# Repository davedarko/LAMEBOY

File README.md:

# LAMEBOY
https://hackaday.io/project/26823-lameboy-another-esp12-handheld

Ever since https://hackaday.io/project/18648-nokia-3310-5110-display-board I've wanted to slap on an ESP module and some buttons to make a nice little portable handheld. Now with some googling and checking out other projects how they get their stuff done and a bit time on hand while on vacation I'm using every spare minute to work on this PCB. There are some minor things I'm not sure about that need testing, but the general concept is clear.

The last version - R 3.2.3 - seems to got lost, it was rebranded to Game Toy and some pinouts were changed to make more sense.

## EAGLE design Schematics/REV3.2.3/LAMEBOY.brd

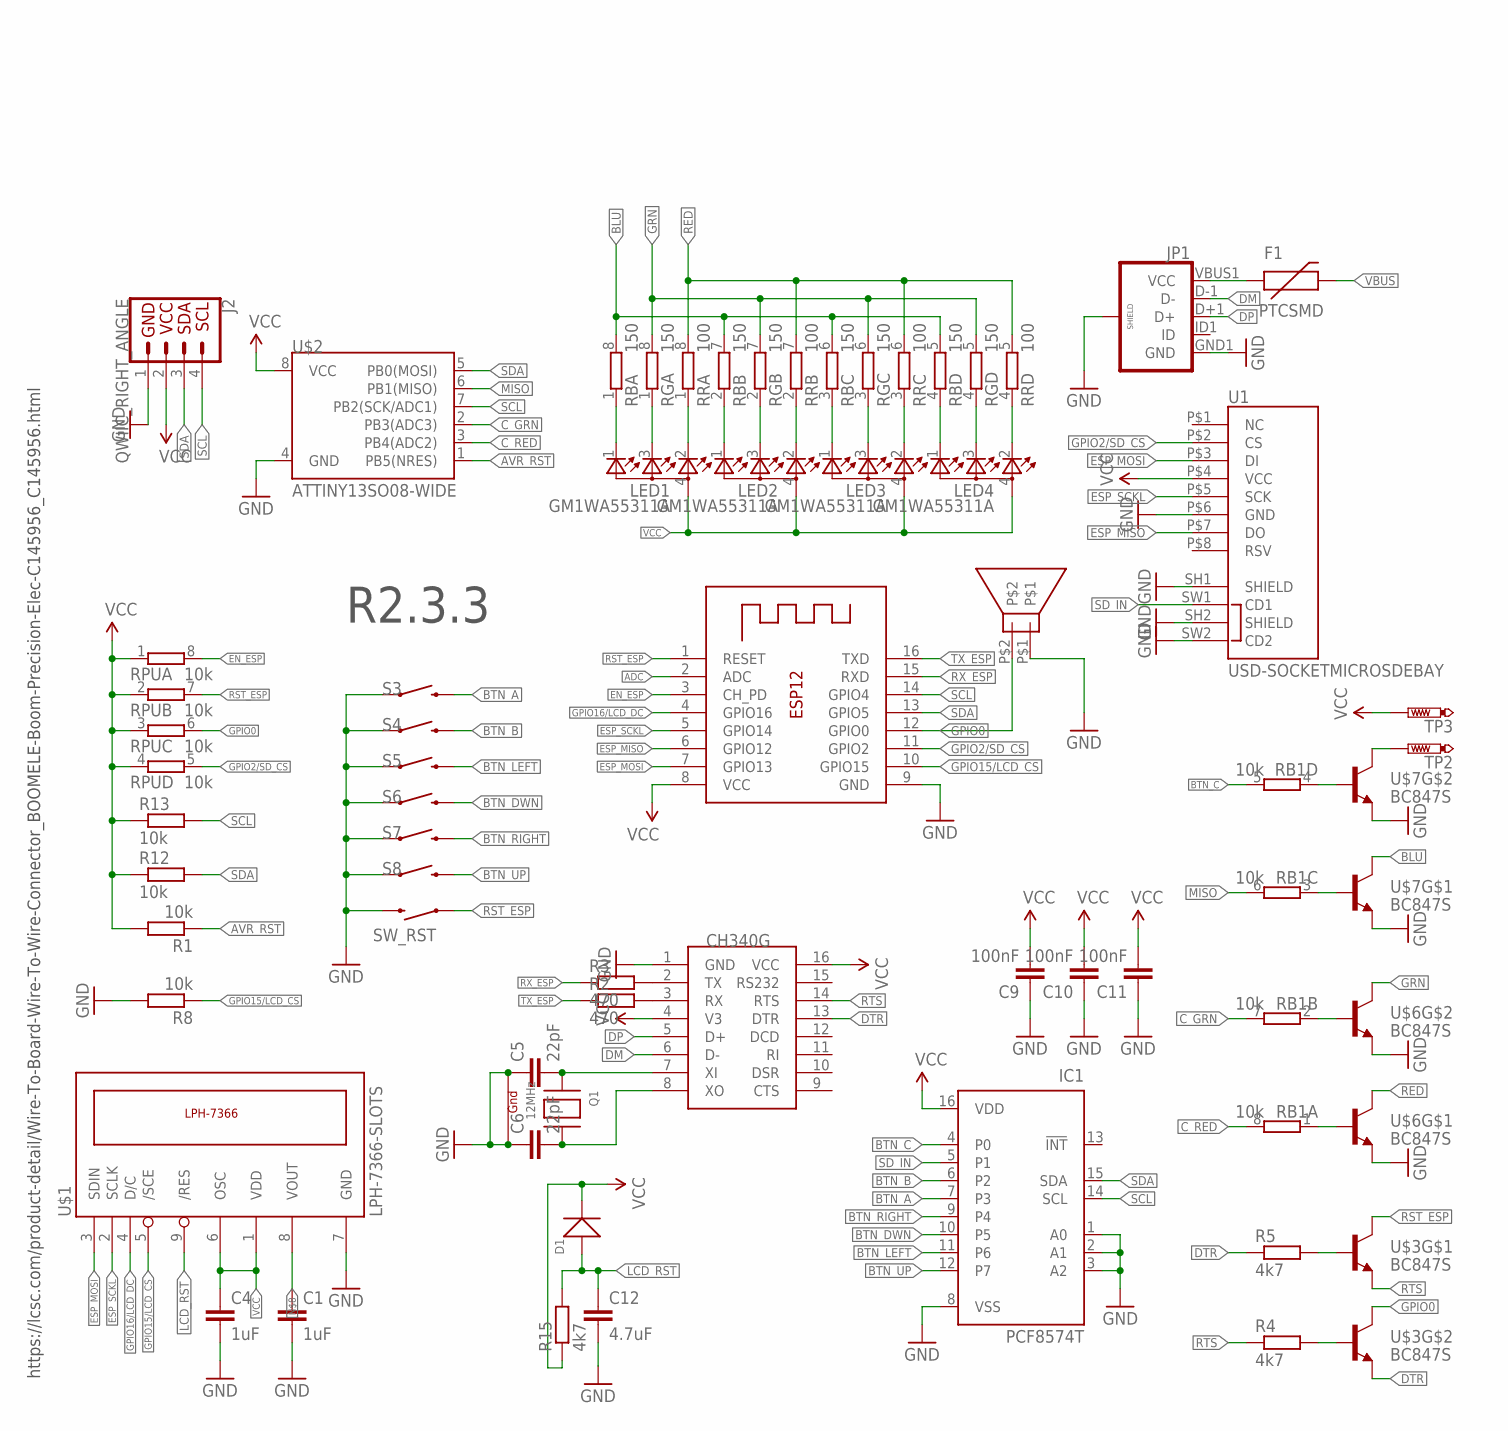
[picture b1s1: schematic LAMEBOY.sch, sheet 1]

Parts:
C1, C4: 1uF; C0805
C5, C6: 22pF; C0805
C9, C10, C11: 100nF; C0805
C12: 4.7uF; C0805
CH340G: CH340GCH340G; SOIC16
D1: DIODE'1N4148-SMD'; LL-34
F1: PTCSMD; PTC-1206
IC1: PCF8574T; SO16W
J2: QWIIC_RIGHT_ANGLE; JST04_1MM_RA
JP1: USB_MICROB_PLUG-IDK; USB-AB-MICRO-SMD_SLOT
LED1, LED2, LED3, LED4: GM1WA55311A
Q1: 12MHz; NX3225_BIGGER
R1, R8, R12, R13: 10k; R0603
R2, R3: 470; R0603
R4, R5, R15: 4k7; R0603
RB: 150; 0603-ARC
RB1: 10k; 0603-ARC
RG: 150; 0603-ARC
RPU: 10k; 0603-ARC
RR: 100; 0603-ARC
S3, S4, S5, S6, S7, S8: SWITCH-MOMENTARY-2SMD-4; TACTILE_SWITCH_TALL
SW_RST: SWITCH-MOMENTARY-2-SMD-1101NE; TACTILE-SWITCH-1101NE
TP2, TP3: PTR1B1,27; B1,27
U1: USD-SOCKETMICROSDEBAY; MICRO-SD-SOCKET-EBAY
U$1: LPH-7366-SLOTS
U$2: ATTINY13SO08-WIDE; SO08-EIAJ
U$3, U$6, U$7: BC847S; SOT363
U$5: SPEAKERKMTG-1102; KMTG-1102
X1: ESP-12

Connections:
ADC: X1.2 (ADC); also elsewhere on the board
AVR_RST: R1.1, U$2.1 (PB5(NRES))
BLU: RB.5 (2), RB.6 (2), RB.7 (2), RB.8 (2), U$7.3 (C)
BLUE_LED: LED4.1 (CGREEN), RB.4 (1)
BTN_A: IC1.7 (P3), S3.B2 (2)
BTN_B: IC1.6 (P2), S4.B2 (2)
BTN_C: IC1.4 (P0), RB1.5 (2)
BTN_DWN: IC1.10 (P5), S6.B2 (2)
BTN_LEFT: IC1.11 (P6), S5.B2 (2)
BTN_RIGHT: IC1.9 (P4), S7.B2 (2)
BTN_UP: IC1.12 (P7), S8.B2 (2)
C_GRN: RB1.7 (2), U$2.2 (PB3(ADC3))
C_RED: RB1.8 (2), U$2.3 (PB4(ADC2))
DM: CH340G.6 (D-), JP1.D-1 (D-)
DP: CH340G.5 (D+), JP1.D+1 (D+)
DTR: CH340G.13 (DTR), R5.1, U$3.1 (E)
EN_ESP: RPU.8 (2), X1.3 (CH_PD)
ESP_MISO: U1.P$7 (DO), X1.6 (GPIO12)
ESP_MOSI: U1.P$3 (DI), U$1.3 (SDIN), X1.7 (GPIO13)
ESP_SCKL: U1.P$5 (SCK), U$1.2 (SCLK), X1.5 (GPIO14)
GND: C1.2, C4.2, C5.1, C6.1, C9.1, C10.1, C11.1, C12.2, CH340G.1 (GND), IC1.1 (A0), IC1.2 (A1), IC1.3 (A2), IC1.8 (VSS), J2.1, JP1.GND1 (GND), JP1.P$1 (SHIELD), JP1.P$2 (SHIELD), JP1.P$3 (SHIELD), JP1.P$4 (SHIELD), Q1.2 (G2), Q1.4 (G1), R8.2, S3.A2 (1), S4.A2 (1), S5.A2 (1), S6.A2 (1), S7.A2 (1), S8.A2 (1), SW_RST.P$2 (2), U1.P$6 (GND), U1.SH1 (SHIELD), U1.SH2 (SHIELD), U1.SW2 (CD2), U$1.7 (GND), U$2.4 (GND), U$5.P$1, U$6.1 (E), U$6.4 (E), U$7.1 (E), U$7.4 (E), X1.9 (GND); also elsewhere on the board
GPIO0: RPU.6 (2), U$3.6 (C), U$5.P$2, X1.12 (GPIO0)
GPIO2/SD_CS: RPU.5 (2), U1.P$2 (CS), X1.11 (GPIO2)
GPIO15/LCD_CS: R8.1, U$1.5 (/SCE), X1.10 (GPIO15)
GPIO16/LCD_DC: U$1.4 (D/C), X1.4 (GPIO16)
GREEN_LED: LED4.3 (CBLUE), RG.4 (1)
GRN: RG.5 (2), RG.6 (2), RG.7 (2), RG.8 (2), U$6.6 (C)
L2_R: LED1.3 (CBLUE), RG.1
L3_B: LED1.1 (CGREEN), RB.1
L4_G: LED1.2 (CRED), RR.1
LCD_RST: C12.1, D1.A (+), R15.2, U$1.9 (/RES)
MISO: RB1.6 (2), U$2.6 (PB1(MISO))
unnamed: LED3.1 (CGREEN), RB.3 (1)
unnamed: LED3.3 (CBLUE), RG.3 (1)
unnamed: LED3.2 (CRED), RR.3 (1)
unnamed: LED2.1 (CGREEN), RB.2 (1)
unnamed: C1.1, U$1.8 (VOUT)
unnamed: LED2.3 (CBLUE), RG.2 (1)
unnamed: LED2.2 (CRED), RR.2 (1)
unnamed: RB1.1, U$6.5 (B)
unnamed: RB1.2 (1), U$6.2 (B)
unnamed: TP2.TP, U$7.6 (C)
unnamed: C5.2, CH340G.7 (XI), Q1.1 (X1)
unnamed: RB1.3 (1), U$7.5 (B)
unnamed: RB1.4 (1), U$7.2 (B)
unnamed: C6.2, CH340G.8 (XO), Q1.3 (X2)
unnamed: R5.2, U$3.5 (B)
unnamed: CH340G.3 (RX), R2.2
unnamed: CH340G.2 (TX), R3.2
unnamed: R4.2, U$3.2 (B)
RED: RR.5 (2), RR.6 (2), RR.7 (2), RR.8 (2), U$6.3 (C)
RED_LED: LED4.2 (CRED), RR.4 (1)
RST_ESP: RPU.7 (2), SW_RST.P$1 (1), U$3.3 (C), X1.1 (RESET)
RTS: CH340G.14 (RTS), R4.1, U$3.4 (E)
RX_ESP: R3.1, X1.15 (RXD)
SCL: IC1.14 (SCL), J2.4, R13.2, U$2.7 (PB2(SCK/ADC1)), X1.14 (GPIO4)
SDA: IC1.15 (SDA), J2.3, R12.2, U$2.5 (PB0(MOSI)), X1.13 (GPIO5)
SD_IN: IC1.5 (P1), U1.SW1 (CD1)
TX_ESP: R2.1, X1.16 (TXD)
VBUS: F1.2; also elsewhere on the board
VCC: C4.1, C9.2, C10.2, C11.2, CH340G.4 (V3), CH340G.16 (VCC), D1.C (-), IC1.16 (VDD), J2.2, LED1.4 (A), LED2.4 (A), LED3.4 (A), LED4.4 (A), R1.2, R12.1, R13.1, R15.1, RPU.1, RPU.2 (1), RPU.3 (1), RPU.4 (1), TP3.TP, U1.P$4 (VCC), U$1.1 (VDD), U$1.6 (OSC), U$2.8 (VCC), X1.8 (VCC); also elsewhere on the board
VUSB: F1.1, JP1.VBUS1 (VCC)

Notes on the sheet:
R2.3.3
https://lcsc.com/product-detail/Wire-To-Board-Wire-To-Wire-Connector_BOOMELE-Boom-Precision-Elec-C145956_C145956.html

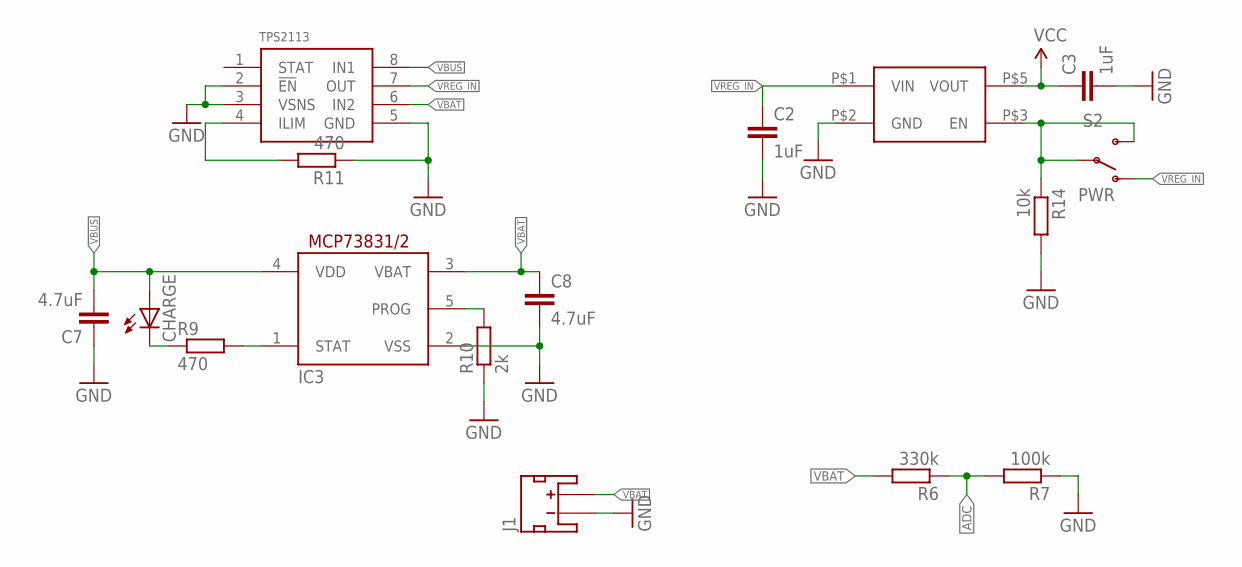
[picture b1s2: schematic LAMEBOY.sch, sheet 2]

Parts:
C2, C3: 1uF; C0805
C7, C8: 4.7uF; C0805
CHARGE: LEDCHARLIE; CHIPLED_0603_CHARLIE
IC3: MCP73831; SOT23-5L
J1: JST_2MM_MALE; JST-2-SMD
R6: 330k; R0603
R7: 100k; R0603
R9, R11: 470; R0603
R10: 2k; R0603
R14: 10k; R0603
S2: PWR; SWITCH-SPST-SMD-A
U$4: TPS2113-PW; TEXAS-PW
U$9: AP2112KAP2112K; AP2112

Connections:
ADC: R6.1, R7.2; also elsewhere on the board
GND: C2.2, C3.2, C7.1, C8.2, IC3.2 (VSS), J1.1 (-), R7.1, R10.1, R11.1, R14.2, U$4.2 (!EN), U$4.3 (VSNS), U$4.5 (GND), U$9.P$2 (GND); also elsewhere on the board
unnamed: IC3.1 (STAT), R9.2
unnamed: CHARGE.C, R9.1
unnamed: R11.2, U$4.4 (ILIM)
unnamed: IC3.5 (PROG), R10.2
VBAT: C8.1, IC3.3 (VBAT), J1.2 (+), R6.2, U$4.6 (IN2)
VBUS: C7.2, CHARGE.A, IC3.4 (VDD), U$4.8 (IN1); also elsewhere on the board
VCC: C3.1, U$9.P$5 (VOUT); also elsewhere on the board
VREG_EN: R14.1, S2.2, S2.3 (S), U$9.P$3 (EN)
VREG_IN: C2.1, S2.1 (O), U$4.7 (OUT), U$9.P$1 (VIN)

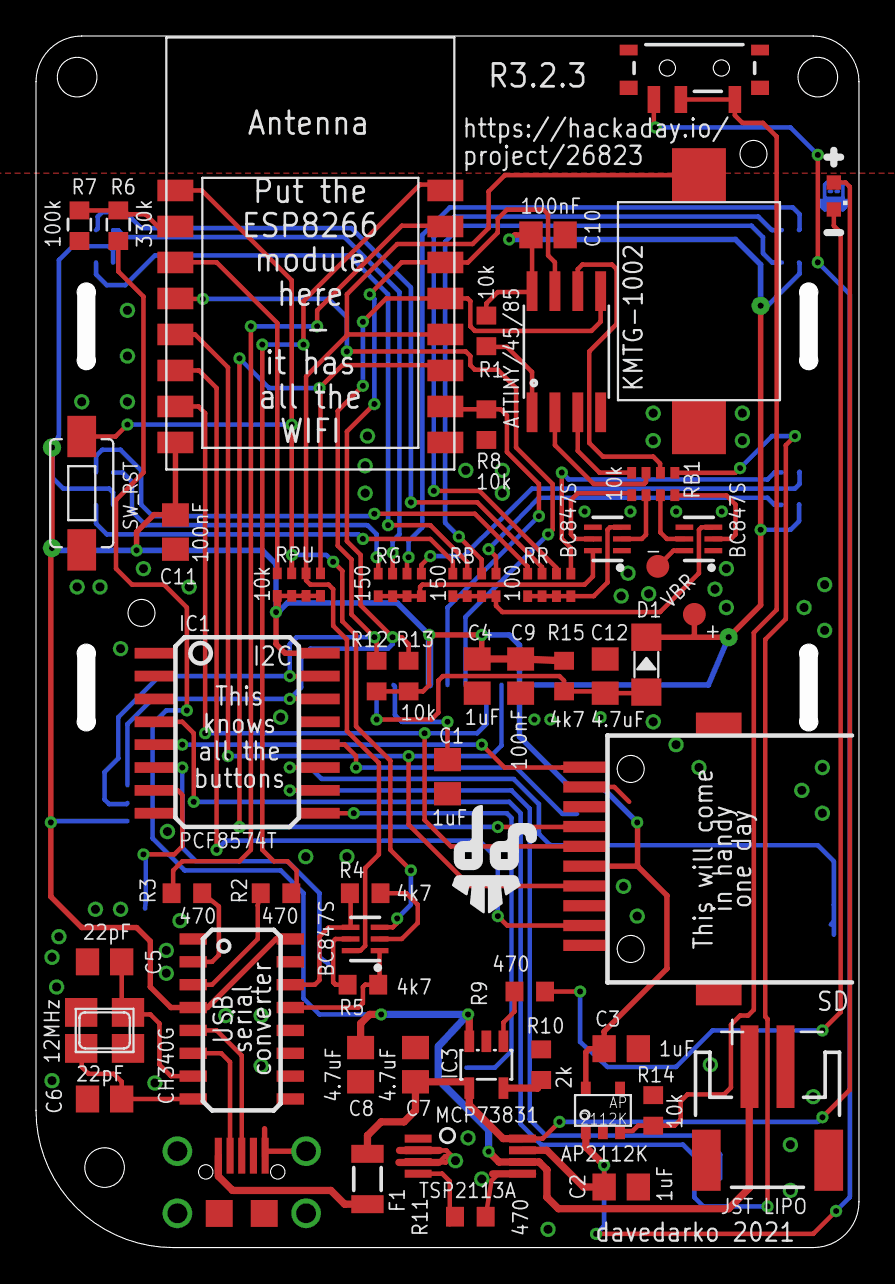
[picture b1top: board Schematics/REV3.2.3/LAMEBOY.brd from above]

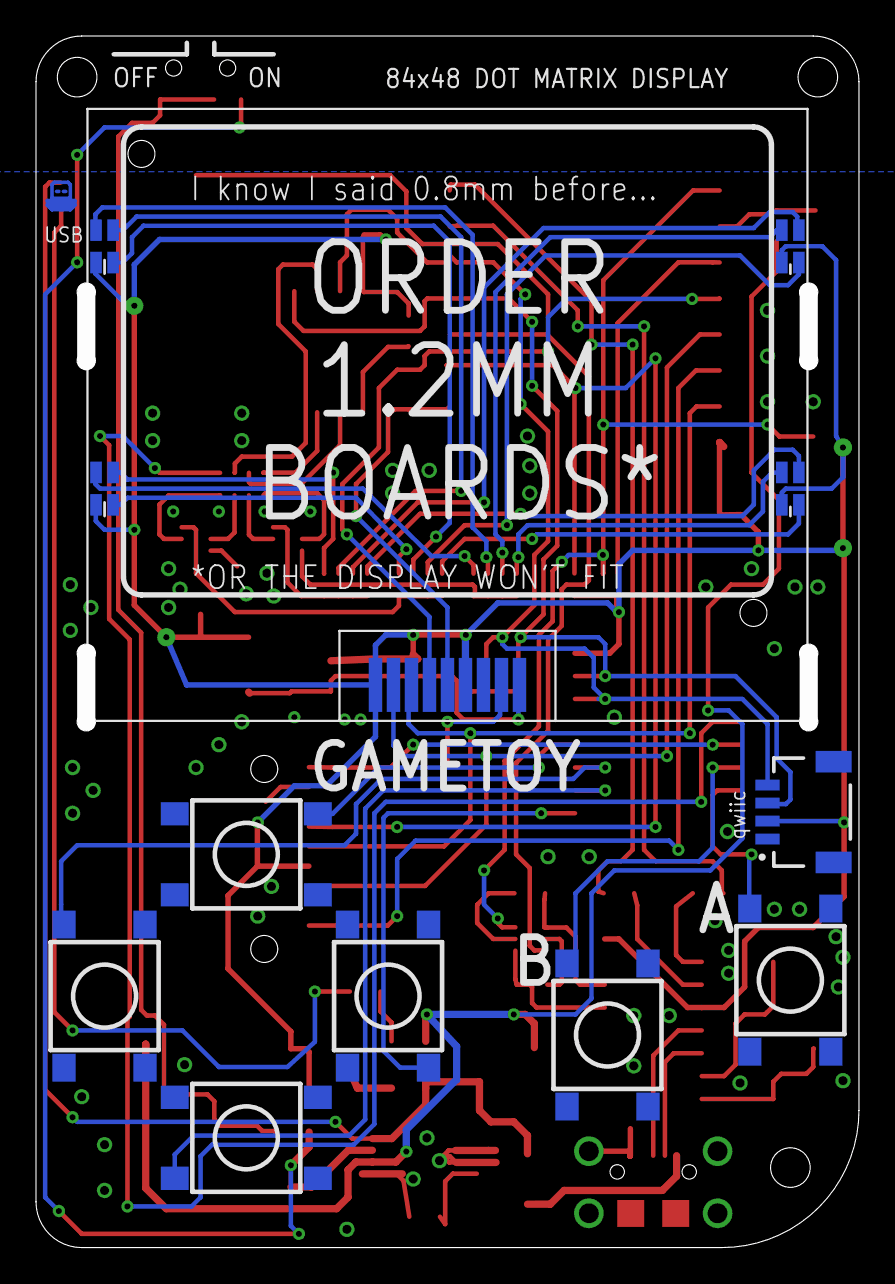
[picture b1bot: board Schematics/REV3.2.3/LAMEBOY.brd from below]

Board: 2 copper layers, 44.7 x 66.3 mm, 68 parts (13 on the bottom side), 69 nets.

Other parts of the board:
U$11: DAVEDARKO2_LOGO
U$13: DAVEDARKO_GOLD

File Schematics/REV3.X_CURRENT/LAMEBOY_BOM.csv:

"Qty";"Value";"Device";"Package";"Parts";"Description";"MF";"MPN";"OC_FARNELL";"OC_NEWARK";"PROD_ID";
"1";"";"ESP-12";"ESP-12";"X1";"";"";"";"";"";"";
"1";"";"JST_2MM_MALE";"JST-2-SMD";"J1";"Mates to single-cell LiPo batteries.";"";"";"";"";"CONN-08352";
"1";"";"LEDCHARLIE";"CHIPLED_0603_CHARLIE";"CHARGE";"LED";"";"";"";"";"";
"2";"";"SWITCH-MOMENTARY-2-SMD-1101NE";"TACTILE-SWITCH-1101NE";"SW_C, SW_RST";"Various NO switches- pushbuttons, reed, etc";"";"";"";"";"";
"1";"100";"4R-N0603-ARC";"0603-ARC";"RR";"Array Chip Resistor";"";"";"unknown";"unknown";"";
"1";"100k";"R-EU_ONEFITSALL";"ONEFITSALL";"R7";"RESISTOR, European symbol";"";"";"";"";"";
"3";"100nF";"C-EUONEFITSALL";"ONEFITSALL";"C9, C10, C11";"CAPACITOR, European symbol";"";"";"";"";"";
"2";"10k";"4R-N0603-ARC";"0603-ARC";"RB1, RPU";"Array Chip Resistor";"";"";"unknown";"unknown";"";
"5";"10k";"R-EU_ONEFITSALL";"ONEFITSALL";"R1, R8, R12, R13, R14";"RESISTOR, European symbol";"";"";"";"";"";
"1";"12MHz";"XTAL-4BIGGER";"NX3225_BIGGER";"Q1";"Classic 4-pin 3.2 x 2.5mm crystal";"";"";"";"";"";
"2";"150";"4R-N0603-ARC";"0603-ARC";"RB, RG";"Array Chip Resistor";"";"";"unknown";"unknown";"";
"4";"1uF";"C-EUONEFITSALL";"ONEFITSALL";"C1, C2, C3, C4";"CAPACITOR, European symbol";"";"";"";"";"";
"2";"22pF";"C-EUONEFITSALL";"ONEFITSALL";"C5, C6";"CAPACITOR, European symbol";"";"";"";"";"";
"1";"2k";"R-EU_ONEFITSALL";"ONEFITSALL";"R10";"RESISTOR, European symbol";"";"";"";"";"";
"1";"330k";"R-EU_ONEFITSALL";"ONEFITSALL";"R6";"RESISTOR, European symbol";"";"";"";"";"";
"2";"4.7uF";"C-EUONEFITSALL";"ONEFITSALL";"C7, C8";"CAPACITOR, European symbol";"";"";"";"";"";
"4";"470";"R-EU_ONEFITSALL";"ONEFITSALL";"R2, R3, R9, R11";"RESISTOR, European symbol";"";"";"";"";"";
"2";"4k7";"R-EU_ONEFITSALL";"ONEFITSALL";"R4, R5";"RESISTOR, European symbol";"";"";"";"";"";
"1";"AP2112KAP2112K";"AP2112KAP2112K";"AP2112";"U$9";"";"";"";"";"";"";
"1";"ATTINY13SO08-WIDE";"ATTINY13SO08-WIDE";"SO08-EIAJ";"U$2";"Atmel 8-pin 1kB flash uC";"";"";"";"";"";
"1";"AVR_SPI_PRG_6";"AVR_SPI_PRG_6";"2X3_SMD_PAD";"JP2";"AVR ISP 6 Pin";"";"";"";"";"";
"3";"BC847S";"MMDT3904";"SOT363";"U$3, U$6, U$7";"Dual NPN transistor";"";"";"";"";"";
"1";"CH340GCH340G";"CH340GCH340G";"SOIC16";"CH340G";"USB to TTL RS232 converter";"";"";"";"";"";
"4";"GM1WA55311A";"GM1WA55311A";"GM1WA55311A";"LED1, LED2, LED3, LED4";"Chip LED RGB";"";"";"";"";"";
"1";"I2C_GROVE";"I2C_GROVE";"I2C_GROVE";"U$10";"";"";"";"";"";"";
"1";"LPH-7366-SLOTS";"LPH-7366-SLOTS";"LPH-7366-SLOTS";"U$1";"";"";"";"";"";"";
"1";"MCP73831";"MCP73831/OT";"SOT23-5L";"IC3";"MCP73831/2";"";"";"";"";"";
"1";"PCF8574T";"PCF8574T";"SO16W";"IC1";"I2C-Bus Remote 8-bit I/O expander";"";"PCF8574T/3,512";"1201255";"70R6870";"";
"1";"PTCSMD";"PTCSMD";"PTC-1206";"F1";"Resettable Fuse PTC";"";"";"";"";"RES-11150";
"1";"PWR";"SWITCH-SPDT-SMD-A";"SWITCH-SPST-SMD-A";"S2";"SPDT Switch";"";"";"";"";"";
"6";"SWITCH-MOMENTARY-2SMD-4";"SWITCH-MOMENTARY-2SMD-4";"TACTILE_SWITCH_TALL";"S3, S4, S5, S6, S7, S8";"Various NO switches- pushbuttons, reed, etc";"";"";"";"";"SWCH-11966";
"1";"TPS2113-PW";"TPS2113-PW";"TEXAS-PW";"U$4";"";"";"";"";"";"";
"1";"USB_MICROB_PLUG-IDK";"USB_MICROB_PLUG-IDK";"USB-AB-MICRO-SMD_SLOT";"JP1";"USB Micro-B connectors";"";"";"";"";"";
"1";"USD-SOCKETMICROSDEBAY";"USD-SOCKETMICROSDEBAY";"MICRO-SD-SOCKET-EBAY";"U1";"microSD Socket";"";"";"";"";"";

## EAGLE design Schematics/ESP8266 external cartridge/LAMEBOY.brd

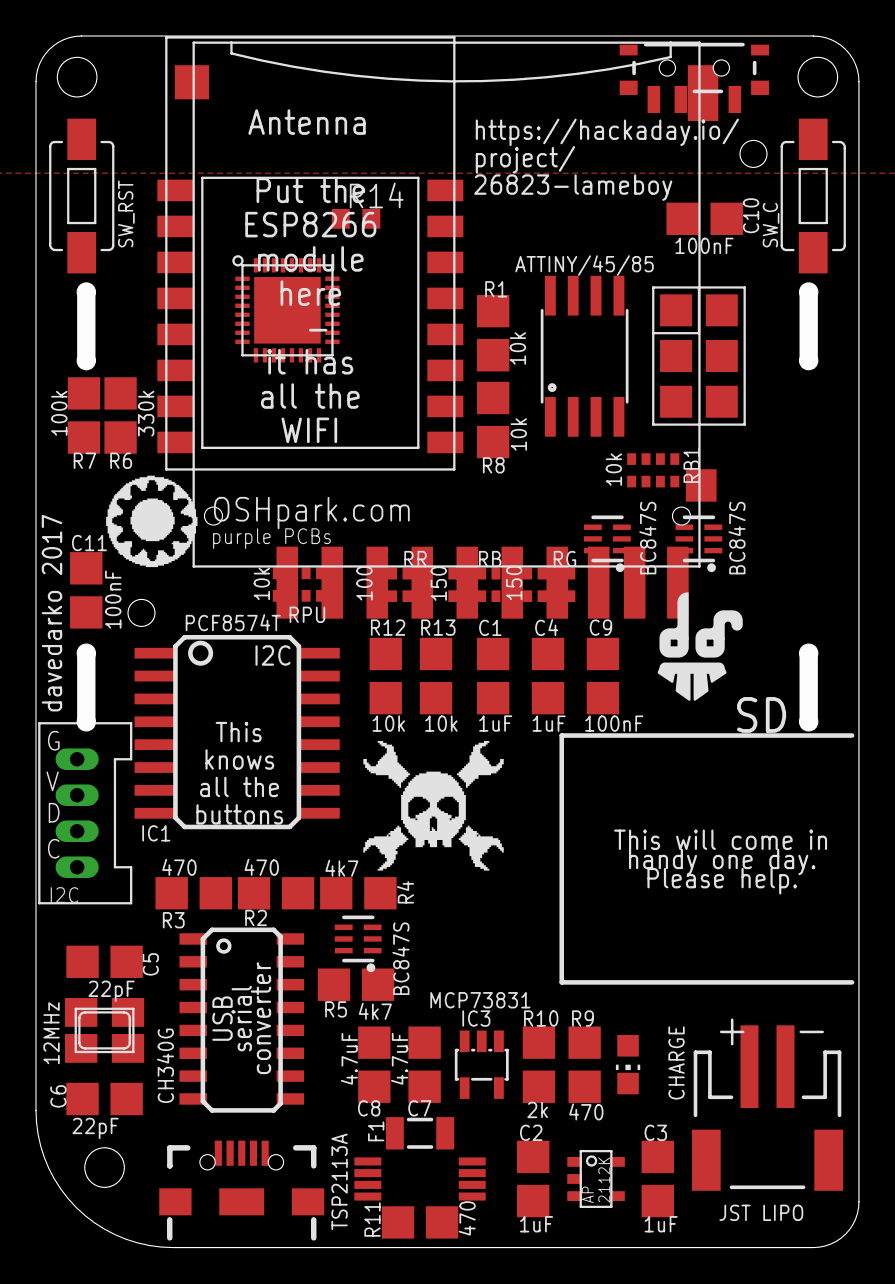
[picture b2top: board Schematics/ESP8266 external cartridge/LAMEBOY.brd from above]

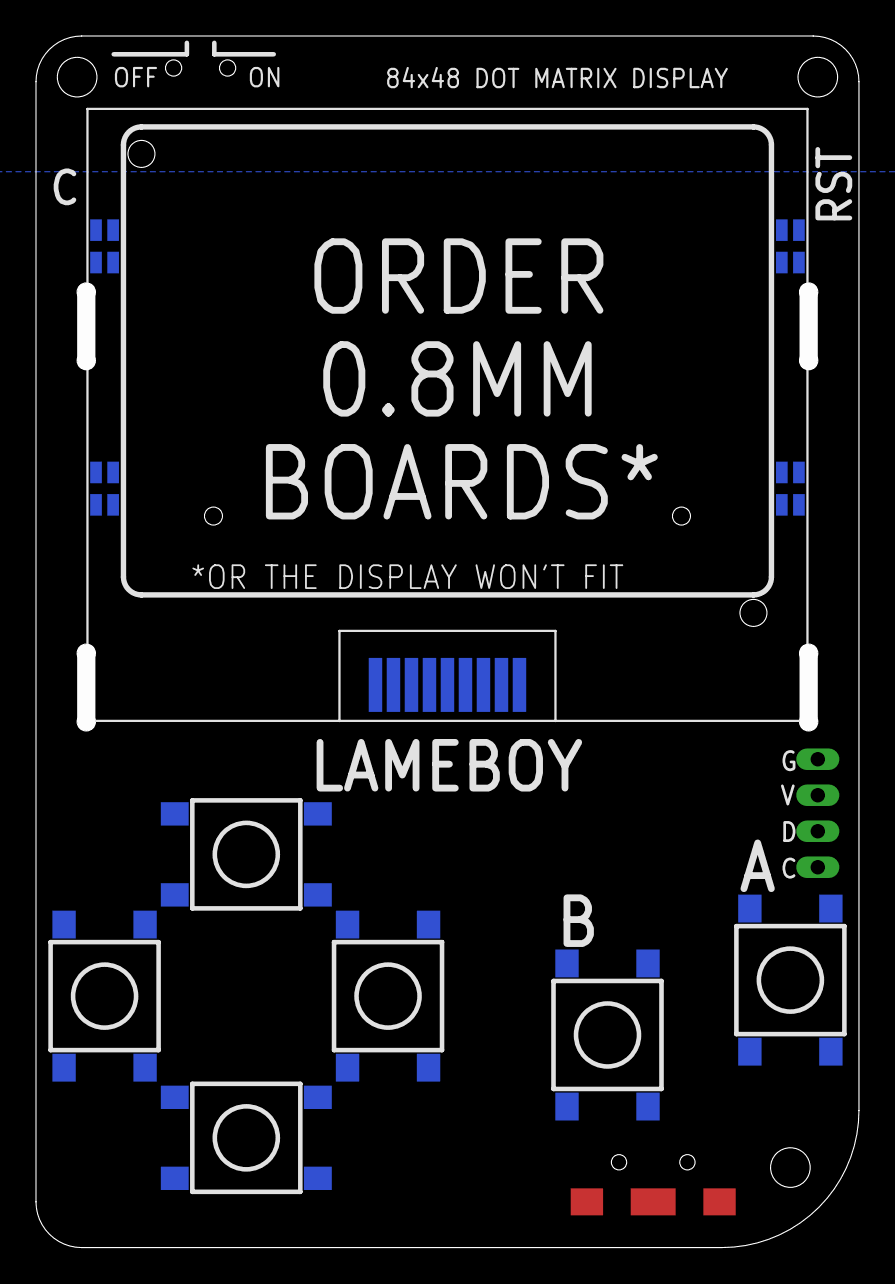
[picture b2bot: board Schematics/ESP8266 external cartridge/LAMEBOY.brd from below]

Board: 2 copper layers, 44.7 x 66.3 mm, 67 parts (12 on the bottom side), 73 nets, no tracks yet.

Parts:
C1, C2, C3, C4: 1uF; ONEFITSALL
C5, C6: 22pF; ONEFITSALL
C7, C8: 4.7uF; ONEFITSALL
C9, C10, C11: 100nF; ONEFITSALL
CH340G: CH340GCH340G; SOIC16
CHARGE: CHIP-LED0805
F1: PTCSMD; PTC-1206
IC1: PCF8574T; SO16W
IC3: MCP73831; SOT23-5L
J1: JST-2-SMD
JP2: AVR_SPI_PRG_6; 2X3_SMD_PAD
LED1, LED2, LED3, LED4: GM1WA55311A
Q1: 12MHz; NX3225_BIGGER
R1, R8, R12, R13: 10k; ONEFITSALL
R2, R3, R9, R11: 470; ONEFITSALL
R4, R5: 4k7; ONEFITSALL
R6: 330k; ONEFITSALL
R7: 100k; ONEFITSALL
R10: 2k; ONEFITSALL
R14: R0603
RB: 150; 0603-ARC
RB1: 10k; 0603-ARC
RG: 150; 0603-ARC
RPU: 10k; 0603-ARC
RR: 100; 0603-ARC
S2: PWR; SWITCH-SPST-SMD-A
S3, S4, S5, S6, S7, S8: SWITCH-MOMENTARY-2SMD-4; TACTILE_SWITCH_TALL
SW_C: TACTILE-SWITCH-1101NE
SW_RST: TACTILE-SWITCH-1101NE
U2: USB; USB-AB-MICRO-SMD_V03
U$1: LPH-7366-SLOTS
U$2: ATTINY13SO08-WIDE; SO08-EIAJ
U$3, U$6, U$7: BC847S; SOT363
U$4: TPS2113-PW; TEXAS-PW
U$5: OSHPARK_LOGO
U$8: DAVEDARKO_GOLD
U$9: AP2112KAP2112K; AP2112
U$10: I2C_GROVE
U$11: DAVEDARKO2_LOGO
U$12: HACKADAY_LOGO
U$13: ESP8266EX
U$14: SDMMCSCDA; SCDA
X1: ESP-12

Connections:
ADC: R6.P$1, R7.P$2, U$13.TOUT, X1.2
AVR_RST: JP2.P$5, R1.P$1, U$2.1
BLU: RB.5, RB.6, RB.7, RB.8, U$7.3
BTN_A: IC1.7, S3.B2
BTN_B: IC1.6, S4.B2
BTN_C: IC1.4, SW_C.P$2
BTN_DWN: IC1.10, S6.B2
BTN_LEFT: IC1.11, S5.B2
BTN_RIGHT: IC1.9, S7.B2
BTN_UP: IC1.12, S8.B2
C_GRN: RB1.8, U$2.2
C_RED: RB1.7, U$2.3
DM: CH340G.6, U2.D-1
DP: CH340G.5, U2.D+1
DTR: CH340G.13, R5.P$1, U$3.1
EN_ESP: RPU.8, U$13.CHIP_EN, X1.3
ESP_MISO: U$13.MTDI, X1.6
ESP_MOSI: U$1.3, U$13.MTCK, X1.7
ESP_SCKL: U$1.2, U$13.MTMS, X1.5
GND: C1.P$2, C2.P$2, C3.P$2, C4.P$2, C5.P$1, C6.P$1, C7.P$1, C8.P$2, C9.P$1, C10.P$1, C11.P$1, CH340G.1, IC1.1, IC1.2, IC1.3, IC1.8, IC3.2, J1.1, JP2.P$6, Q1.2, Q1.4, R7.P$1, R8.P$2, R10.P$1, R11.P$1, RB1.5, S3.A2, S4.A2, S5.A2, S6.A2, S7.A2, S8.A2, SW_C.P$1, SW_RST.P$2, U2.GND1, U$1.7, U$2.4, U$4.2, U$4.3, U$4.5, U$6.1, U$6.4, U$7.1, U$7.4, U$7.6, U$9.P$2, U$10.P$1, U$13.GND, U$14.3, U$14.6, U$14.13, X1.9
GPIO0: RPU.6, U$1.9, U$3.6, U$13.GPIO0, X1.12
GPIO2: RPU.5, U$1.4, U$13.GPIO2, X1.11
GPIO15: R8.P$1, U$1.5, U$13.MTDO, X1.10
GRN: RG.5, RG.6, RG.7, RG.8, U$6.3
L2_R: LED1.3, RR.1
L3_B: LED1.1, RB.1
L4_G: LED1.2, RG.1
MISO: JP2.P$1, RB1.6, U$2.6
unnamed: LED4.1, RB.4
unnamed: LED4.3, RR.4
unnamed: LED4.2, RG.4
unnamed: LED3.1, RB.3
unnamed: LED3.3, RR.3
unnamed: LED3.2, RG.3
unnamed: LED2.1, RB.2
unnamed: C1.P$1, U$1.8
unnamed: LED2.3, RR.2
unnamed: LED2.2, RG.2
unnamed: RB1.1, U$6.5
unnamed: IC3.1, R9.P$2
unnamed: RB1.2, U$6.2
unnamed: U$13.VDD3P3_1, U$13.VDD3P3_2, U$13.VDDA, U$13.VDDA_2, U$13.VDDD, U$13.VDDPST, U$13.VDDPST_2
unnamed: CHARGE.C, R9.P$1
unnamed: C5.P$2, CH340G.7, Q1.1
unnamed: RB1.3, U$7.5
unnamed: RB1.4, U$7.2
unnamed: R11.P$2, U$4.4
unnamed: IC3.5, R10.P$2
unnamed: R14.1, U$13.SDIO_CLK
unnamed: C6.P$2, CH340G.8, Q1.3
unnamed: R5.P$2, U$3.5
unnamed: CH340G.3, R2.P$2
unnamed: CH340G.2, R3.P$2
unnamed: R4.P$2, U$3.2
RED: RR.5, RR.6, RR.7, RR.8, U$6.6
RST_ESP: RPU.7, SW_RST.P$1, U$3.3, X1.1
RTS: CH340G.14, R4.P$1, U$3.4
RX_ESP: R3.P$1, U$13.U0RXD, X1.15
SCL: IC1.14, JP2.P$3, R13.P$2, U$2.7, U$10.P$4, U$13.GPIO4, X1.14
SDA: IC1.15, JP2.P$4, R12.P$2, U$2.5, U$10.P$3, U$13.GPIO5, X1.13
SD_!HD: U$13.SDIO_DATA_2, U$14.8
SD_!WP: U$13.SDIO_DATA_3, U$14.9
SD_CLK: R14.2, U$14.5
SD_CS0: U$13.SDIO_CMD, U$14.1
SD_SI: U$13.SDIO_DATA_1, U$14.2
SD_SO: U$13.SDIO_DATA_0, U$14.7
TX_ESP: R2.P$1, U$13.U0TXD, X1.16
VBAT: C8.P$1, IC3.3, J1.2, R6.P$2, U$4.6
VBUS: C7.P$2, CHARGE.A, F1.2, IC3.4, U$4.8
VCC: C3.P$1, C4.P$1, C9.P$2, C10.P$2, C11.P$2, CH340G.4, CH340G.16, IC1.16, JP2.P$2, LED1.4, LED2.4, LED3.4, LED4.4, R1.P$2, R12.P$1, R13.P$1, RPU.1, RPU.2, RPU.3, RPU.4, S2.1, U$1.1, U$1.6, U$2.8, U$9.P$5, U$10.P$2, U$14.4, X1.8
VREG_EN: S2.2, S2.3, U$9.P$3
VREG_IN: C2.P$1, U$4.7, U$9.P$1
VUSB: F1.1, U2.VBUS1

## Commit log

2017-09-26 rev2
2017-10-04 bigger better resistor and crystal footprint
2017-10-14 no idea. there's stuff changed so I push.
2017-10-20 idea of an external cartridge
2017-10-20 corrected rgb layout
2017-10-20 moved sd slot slightley
2017-10-20 moved a via :D
2017-10-20 labelstuff
2017-10-21 moved C and RST switch
2017-10-21 usb logo
2017-10-21 read me
2017-10-23 wrong power for enabling regulator
2017-10-25 layerstuff and footprints
2018-01-09 hm, what happened here
2018-01-24 moved 3.1 to 3.X
    added pull down power switch
2018-02-20 minor changes to rev3.1
2018-02-20 rev3.4 sound pins
2018-02-20 external cartridge
2018-02-20 case designs
2018-02-20 attiny binary
2018-02-20 label for batteries
2018-02-20 moar labels
2018-02-21 moaar labels
2018-03-10 current version gerber
2018-03-10 minor footprint changes
2018-03-11 current bom
2019-08-22 sound and vibrator
2019-08-30 bye c
2020-01-10 moved labels
2024-09-05 added KiCad Schematics of R3.2.1
2024-09-08 found the last version!

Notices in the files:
parts and their libraries:
SparkFun-Connectors: Licensing: Creative Commons ShareAlike 4.0 International - https://creativecommons.org/licenses/by-sa/4.0
